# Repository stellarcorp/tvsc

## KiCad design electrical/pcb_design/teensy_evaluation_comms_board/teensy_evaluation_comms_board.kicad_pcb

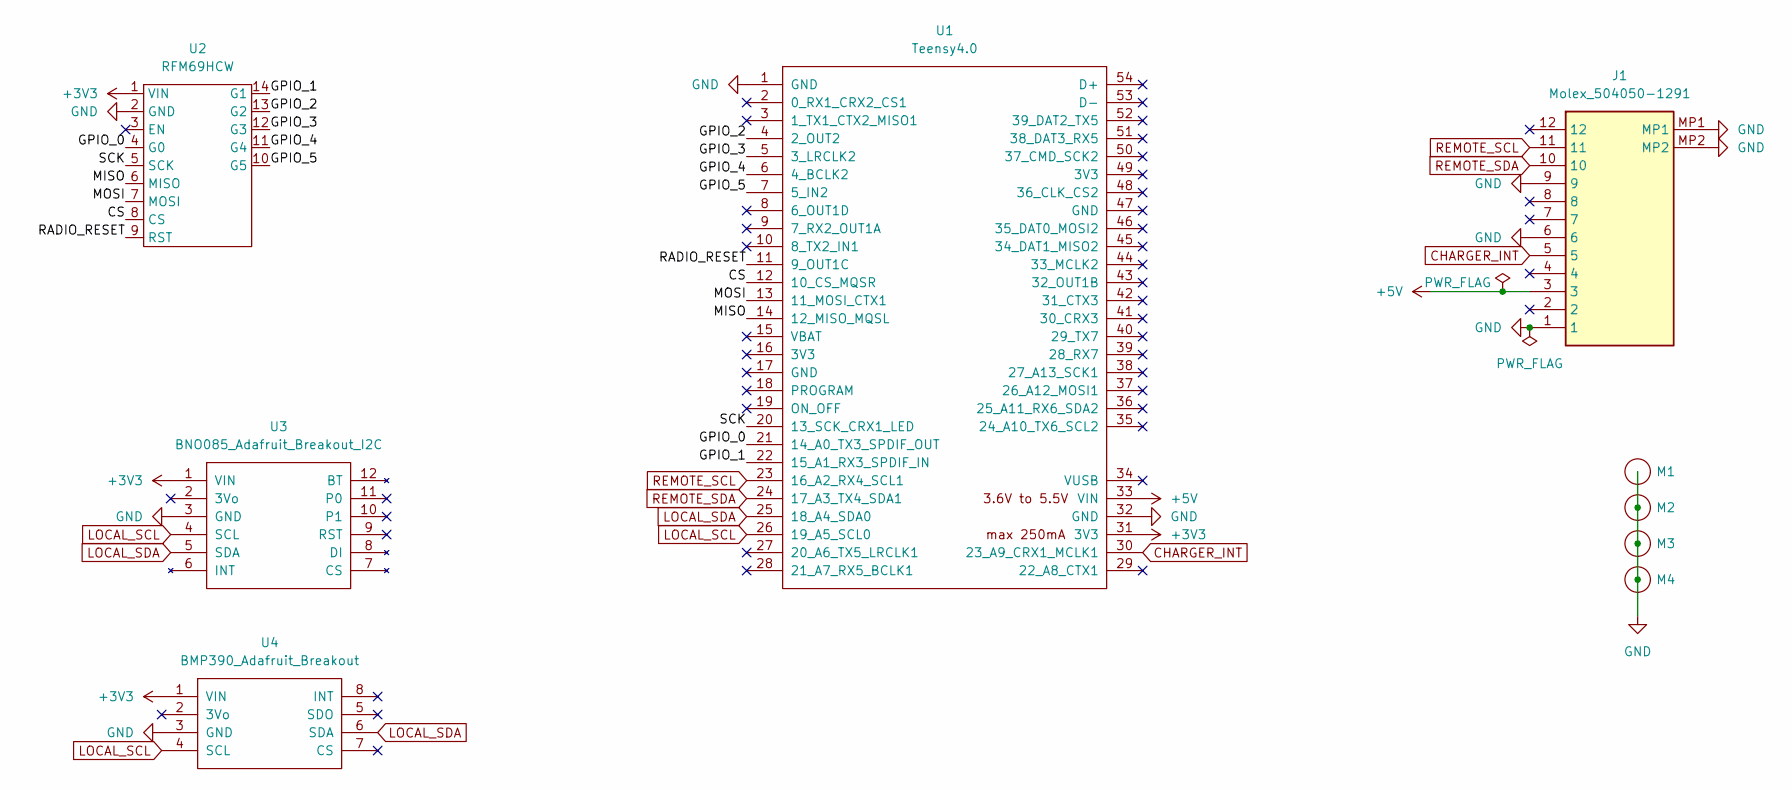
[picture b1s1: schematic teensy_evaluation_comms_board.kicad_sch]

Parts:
J1: Molex_504050-1291; 5040501291; Manufacturer_Part_Number 504050-1291; Mouser Part Number 538-504050-1291
M1, M2, M3, M4: MountingHole_3.2mm_M3_ISO7380_Pad_TopBottom
U1: Teensy4.0; Teensy40
U2: RFM69HCW; RFM69HCW_Adafruit_Breakout
U3: BNO085_Adafruit_Breakout_I2C; BNO085_Adafruit_Breakout
U4: BMP390_Adafruit_Breakout

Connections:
+3V3: U1.31 (3V3), U2.1 (VIN), U3.1 (VIN), U4.1 (VIN)
+5V: J1.3, U1.33 (VIN)
/CS: U1.12 (10_CS_MQSR), U2.8 (CS)
/GPIO_0: U1.21 (14_A0_TX3_SPDIF_OUT), U2.4 (G0)
/GPIO_1: U1.22 (15_A1_RX3_SPDIF_IN), U2.14 (G1)
/GPIO_2: U1.4 (2_OUT2), U2.13 (G2)
/GPIO_3: U1.5 (3_LRCLK2), U2.12 (G3)
/GPIO_4: U1.6 (4_BCLK2), U2.11 (G4)
/GPIO_5: U1.7 (5_IN2), U2.10 (G5)
/MISO: U1.14 (12_MISO_MQSL), U2.6 (MISO)
/MOSI: U1.13 (11_MOSI_CTX1), U2.7 (MOSI)
/RADIO_RESET: U1.11 (9_OUT1C), U2.9 (RST)
/SCK: U1.20 (13_SCK_CRX1_LED), U2.5 (SCK)
CHARGER_INT: J1.5, U1.30 (23_A9_CRX1_MCLK1)
GND: J1.1, J1.6, J1.9, J1.MP1, J1.MP2, M1.1 (Hole), M2.1 (Hole), M3.1 (Hole), M4.1 (Hole), U1.1 (GND), U1.32 (GND), U2.2 (GND), U3.3 (GND), U4.3 (GND)
LOCAL_SCL: U1.26 (19_A5_SCL0), U3.4 (SCL), U4.4 (SCL)
LOCAL_SDA: U1.25 (18_A4_SDA0), U3.5 (SDA), U4.6 (SDA)
REMOTE_SCL: J1.11, U1.23 (16_A2_RX4_SCL1)
REMOTE_SDA: J1.10, U1.24 (17_A3_TX4_SDA1)

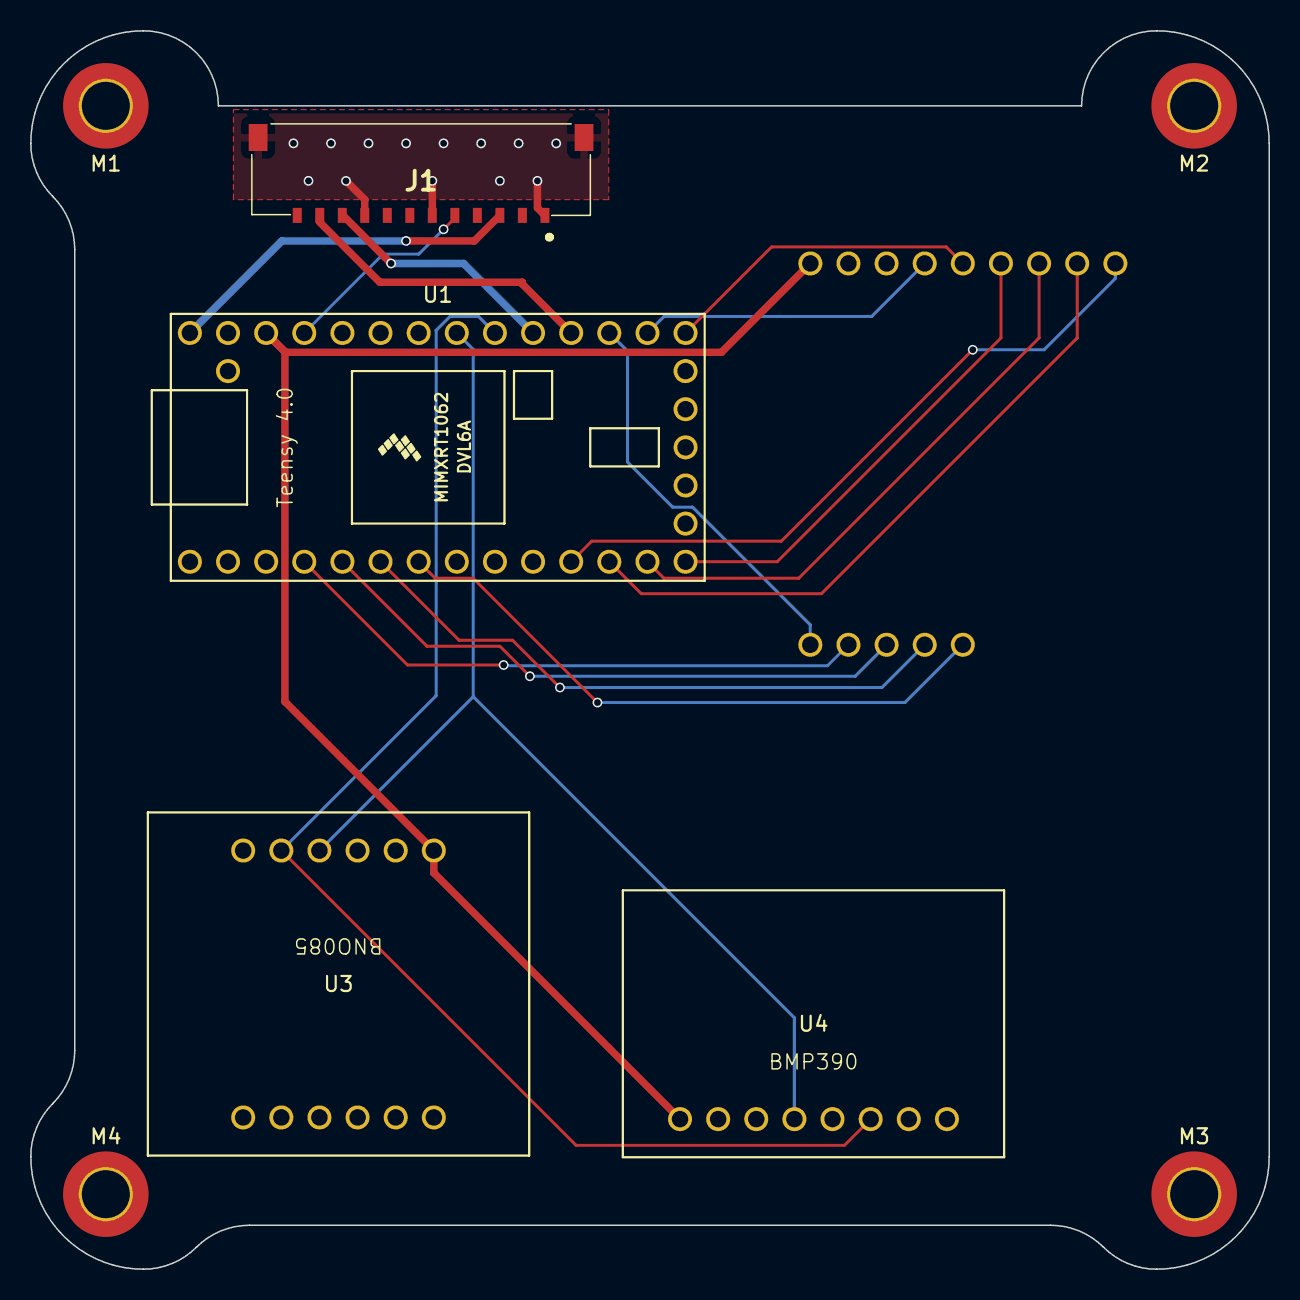
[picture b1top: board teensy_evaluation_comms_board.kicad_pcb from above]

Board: 2 copper layers, 82.5 x 82.5 mm, 9 parts (1 on the bottom side), 19 nets.

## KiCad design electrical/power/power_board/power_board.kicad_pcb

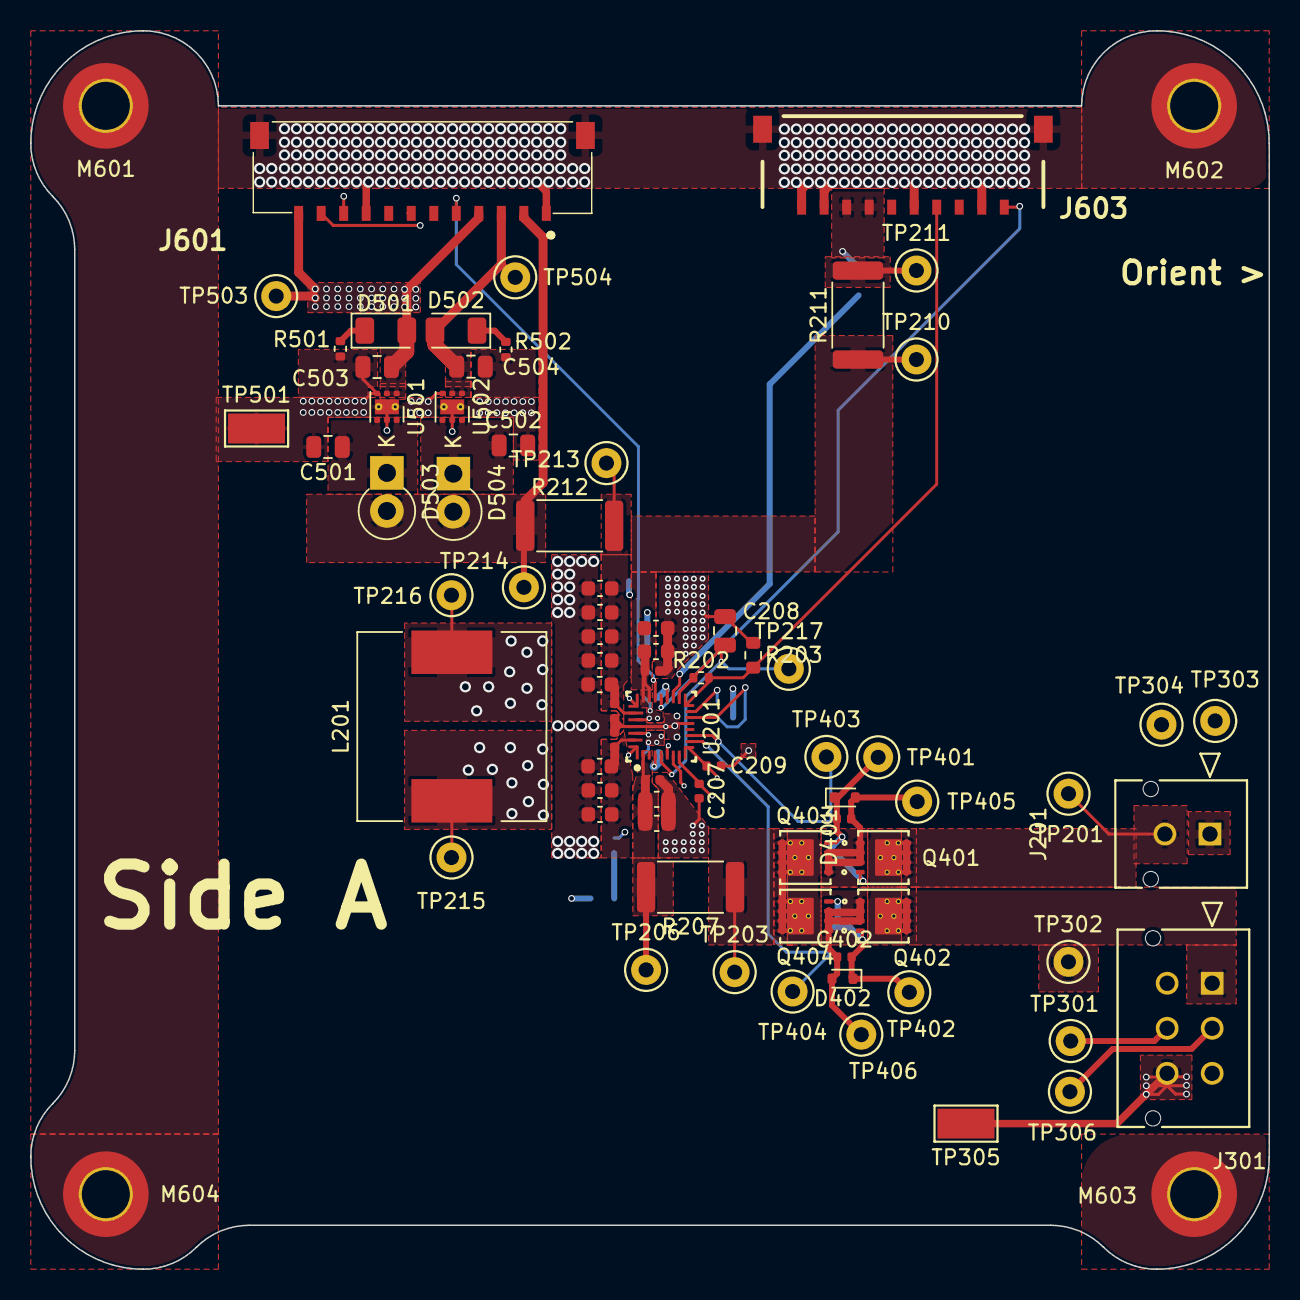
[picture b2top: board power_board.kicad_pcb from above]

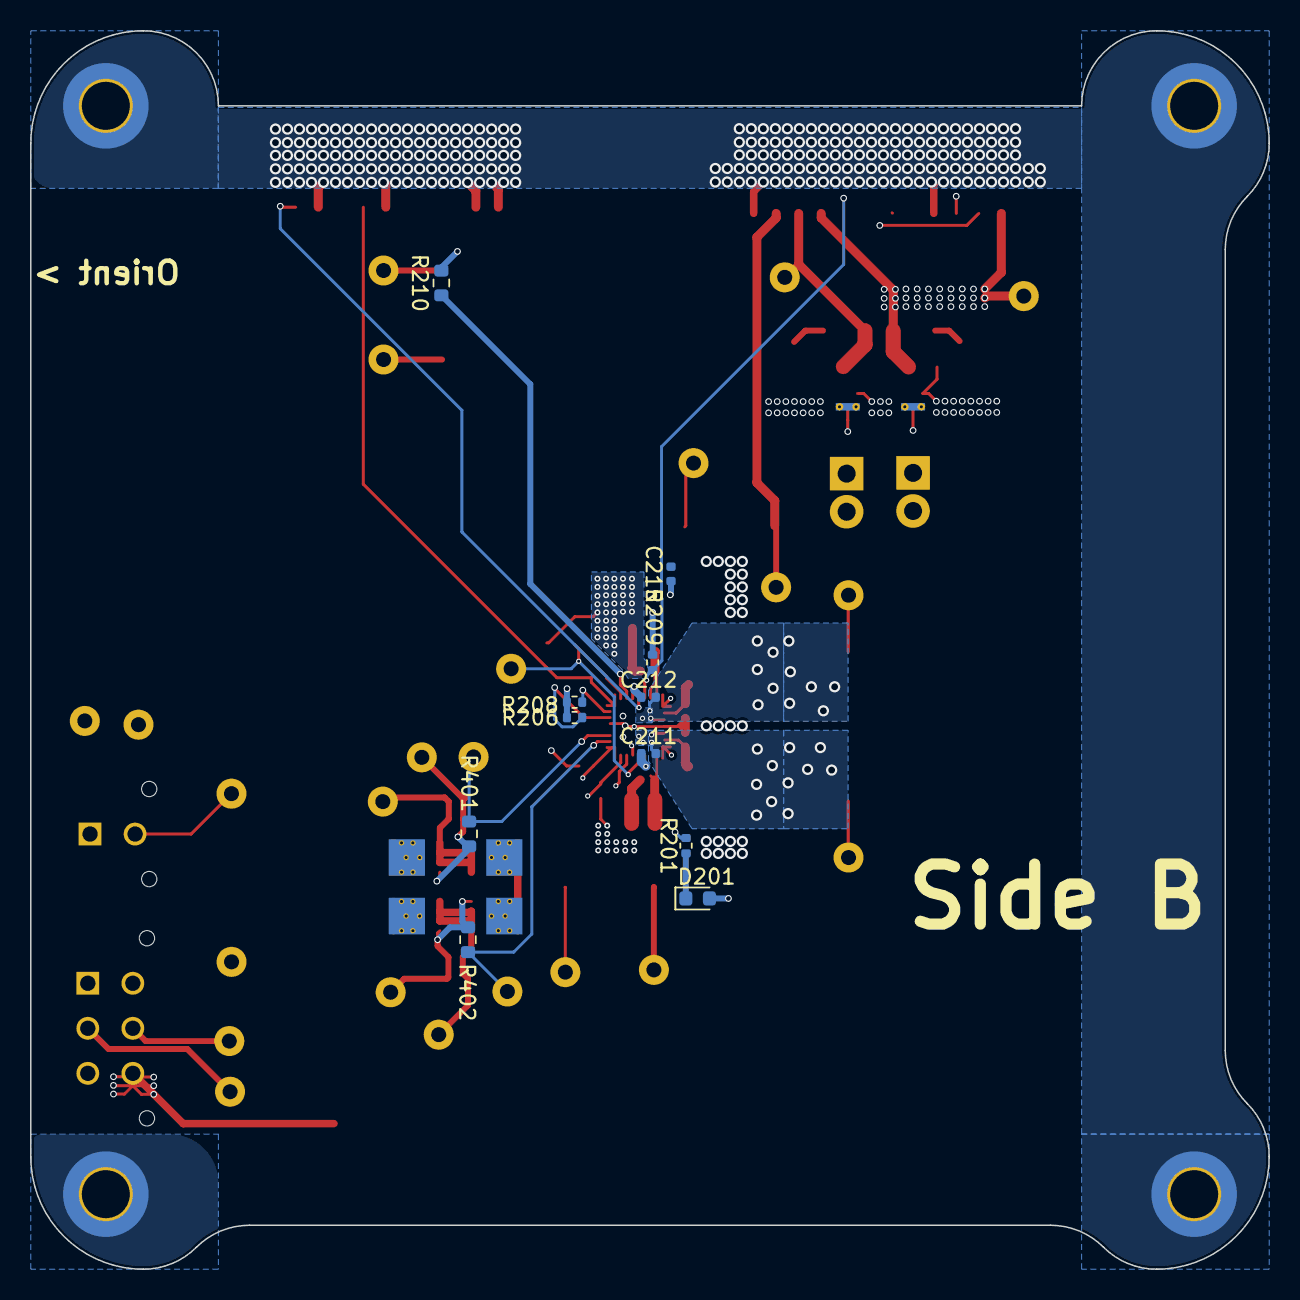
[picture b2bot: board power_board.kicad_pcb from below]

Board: 4 copper layers, 82.5 x 82.5 mm, 90 parts (11 on the bottom side), 40 nets.

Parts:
C201, C202, C203, C205, C206, C214, C216, C217, C218, C219, C220, C221: 10u; C_0603_1608Metric
C204, C207, C209, C210, C213, C222: 0.1u; C_0402_1005Metric
C208: 4.7u; C_0805_2012Metric
C211, C212: 0.047u; C_0402_1005Metric
C215, C401, C402: 1n; C_0402_1005Metric
C501, C502: 1u; C_0805_2012Metric
C503, C504: 2.2u; C_0805_2012Metric
D201: Green LED; LED_0603_1608Metric
D401, D402: 12V; D_SOD-523
D501, D502: White LED; LED_1206_3216Metric
D503, D504: 3A; D_DO-15_P2.54mm_Vertical_KathodeUp
J201: Molex_430450212
J301: Molex_430450612
J601: 504050-1291; 5040501291
J603: 504050-1091
L201: 1uH; L_12x12mm_H8mm
M601, M602, M603, M604: MountingHole_3.2mm_M3_ISO7380_Pad_TopBottom
Q401, Q402, Q403, Q404: CSD17581Q3A; Q3A_TEX
R201: 2.21k; R_0402_1005Metric
R202: 5.24k; R_0402_1005Metric
R203: 30.31k; R_0603_1608Metric
R206, R208, R209: 10k; R_0402_1005Metric
R207, R211, R212: 0.01; R_2512_6332Metric
R210: 100; R_0603_1608Metric
R401, R402: 294; R_0603_1608Metric
R501: 68; R_0402_1005Metric
R502: 150; R_0402_1005Metric
TP201, TP203, TP206, TP210, TP211, TP213, TP214, TP215, TP216, TP217, TP303, TP304, TP405, TP406: White; TestPoint_Keystone_5000-5004_Miniature
TP301, TP306, TP403, TP404: Black; TestPoint_Keystone_5000-5004_Miniature
TP302, TP401, TP402, TP503, TP504: Red; TestPoint_Keystone_5000-5004_Miniature
TP305, TP501: Ring; TestPoint_Keystone_5019_Minature
U201: BQ25798RQMR; RQM0029A-MFG
U501: TLV76733DRVx; WSON-6-1EP_2x2mm_P0.65mm_EP1x1.6mm_ThermalVias
U502: TLV76750DRVx; WSON-6-1EP_2x2mm_P0.65mm_EP1x1.6mm_ThermalVias

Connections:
+3.3V: C503.1, D201.2 (A), D501.2 (A), J601.4, J601.12, R206.1, R208.1, R209.1, TP503.1, U501.1 (OUT), U501.2 (SNS)
+5V: C504.1, D502.2 (A), J601.3, TP504.1, U502.1 (OUT), U502.2 (SNS)
/Charger/BAT: C216.1, C218.1, C222.1, R211.1, TP210.1, U201.22 (BAT), U201.23 (BAT)
/Charger/BATP: R210.1, U201.18 (BATP)
/Charger/BTST1: C211.1, U201.4 (BTST1)
/Charger/BTST2: C212.1, U201.19 (BTST2)
/Charger/PMID: C201.1, C202.1, C203.1, C204.1, U201.29 (PMID)
/Charger/REGN: C208.1, R202.1, TP217.1, U201.5 (REGN), U201.17 (ILIM_HIZ)
/Charger/STAT: R201.2, U201.1 (STAT)
/Charger/SW1: C211.2, L201.1, TP215.1, U201.28 (SW1)
/Charger/SW2: C212.2, L201.2, TP216.1, U201.26 (SW2)
/Charger/SYS: C213.1, C214.1, C217.1, C219.1, C220.1, C221.1, R212.1, TP213.1, U201.25 (SYS)
/Charger/VBUS_PIN: C205.1, C206.1, C210.1, R207.2, TP206.1, U201.2 (VBUS), U201.3 (VBUS)
/Input Selection/ACDRV1_SOURCE: C401.1, D401.2 (A), Q401.1 (S), Q403.1 (S), TP405.1
/Input Selection/ACDRV2_SOURCE: C402.1, D402.2 (A), Q402.1 (S), Q404.1 (S), TP406.1
/Input Selection/SOLAR_VBUS_GATE: C401.2, D401.1 (K), Q401.4 (G), Q403.4 (G), R401.1, TP401.1
/Input Selection/USB_VBUS_GATE: C402.2, D402.1 (K), Q402.4 (G), Q404.4 (G), R402.1, TP402.1
/USB/USB_CC1: J301.2, TP306.1
/USB/USB_CC2: J301.5, TP301.1
ACDRV1: R401.2, TP403.1, U201.11 (ACDRV1)
ACDRV2: R402.2, TP404.1, U201.10 (ACDRV2)
BATTERY_+: J603.3, J603.4, R210.2, R211.2, TP211.1
BATTERY_ID: J603.10, U201.20 (PROG)
CHARGER_INT: J601.5, R209.2, U201.21 (INT_N)
GND: C201.2, C202.2, C203.2, C204.2, C205.2, C206.2, C207.2, C208.2, C209.2, C210.2, C213.2, C214.2, C215.2, C216.2, C217.2, C218.2, C219.2, C220.2, C221.2, C222.2, C501.2, C502.2, C503.2, C504.2, J201.1, J301.6, J601.1, J601.6, J601.9, J601.MP1, J601.MP2, J603.1, J603.2, J603.6, J603.9, J603.11 (MP1), J603.12 (MP2), M601.1 (Hole), M602.1 (Hole), M603.1 (Hole), M604.1 (Hole), R203.2, R501.2, R502.2, TP305.1, TP501.1, U201.13 (CE_N), U201.27 (GND), U501.3 (GND), U501.5 (GND), U501.7 (PAD), U502.3 (GND), U502.5 (GND), U502.7 (PAD)
unnamed: D201.1 (K), R201.1
unnamed: D501.1 (K), R501.1
unnamed: D502.1 (K), R502.1
unnamed: C501.1, D503.1 (K), U501.4 (EN), U501.6 (IN)
unnamed: C502.1, D504.1 (K), U502.4 (EN), U502.6 (IN)
unnamed: C215.1, U201.24 (SDRV)
POWER_SCL: J601.11, R206.2, U201.14 (SCL)
POWER_SDA: J601.10, R208.2, U201.15 (SDA)
SOLAR_VBUS: C209.1, J201.2, Q401.5 (D), TP201.1, U201.9 (VAC1)
THERMISTOR: J603.7, R202.2, R203.1, U201.16 (TS)
USB_D+: J301.3, TP303.1, U201.6 (D+)
USB_D-: J301.4, TP304.1, U201.7 (D-)
USB_VBUS: C207.1, J301.1, Q402.5 (D), TP302.1, U201.8 (VAC2)
VBUS: Q403.5 (D), Q404.5 (D), R207.1, TP203.1
VCC: D503.2 (A), D504.2 (A), J601.2, R212.2, TP214.1

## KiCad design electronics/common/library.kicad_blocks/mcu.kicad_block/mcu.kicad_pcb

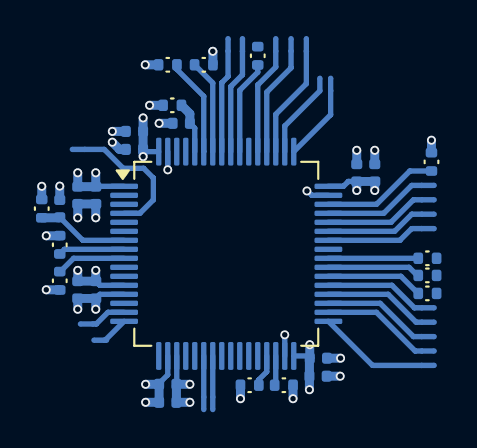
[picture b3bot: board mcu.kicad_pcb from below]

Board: 4 copper layers, 49 parts (49 on the bottom side), 36 nets.

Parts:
C101, C102, C105, C106, C108, C109, C111, C112: 100n; Nondescript_C_0402_1005Metric
C103, C104, C107, C110, C113, C114: 1u; Nondescript_C_0402_1005Metric
NT101, NT102, NT103, NT104, NT105, NT106, NT107, NT108, NT109, NT110, NT111, NT112, NT113, NT114, NT115, NT116, NT117, NT118, NT119, NT120, NT121: NetTie_2; NetTie-2_SMD_Pad0.3mm
R101, R105, R106, R107, R108, R109, R110, R111, R112: 9k31; Nondescript_R_0402_1005Metric
R102, R103, R104, R113: 33; Nondescript_R_0402_1005Metric
U101: STM32L452RCTx; LQFP-64_10x10mm_P0.5mm

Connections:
/mcu/3V3: C103.1, C104.1, C105.1, C106.1, C107.1, C108.1, C109.1, C110.1, C111.1, C112.1, C113.1, C114.1, R101.1, R105.1, R107.1, R108.1, R109.1, R110.1, R111.1, R112.1, U101.1 (VBAT), U101.13 (VDDA), U101.19 (VDD), U101.32 (VDD), U101.48 (VDDUSB), U101.64 (VDD)
/mcu/BOARD_ID_PWR_INTERNAL: NT111.1, U101.22 (PA6)
/mcu/BOARD_ID_SENS_INTERNAL: NT112.1, U101.23 (PA7)
/mcu/BOARD_ID_VERSION_INTERNAL: NT110.1, U101.16 (PA2)
/mcu/BOOT0: C101.1, R106.1, U101.60 (PH3)
/mcu/CAN1_RX_INTERNAL: NT108.1, U101.44 (PA11)
/mcu/CAN1_SHUTDOWN_INTERNAL: NT106.1, U101.42 (PA9)
/mcu/CAN1_SILENT_INTERNAL: NT107.1, U101.43 (PA10)
/mcu/CAN1_TX_INTERNAL: NT109.1, U101.45 (PA12)
/mcu/DEBUG_LED_INTERNAL: NT105.2, U101.4 (PC15)
/mcu/I2C1_SCL: R108.2, U101.58 (PB6)
/mcu/I2C1_SDA: R111.2, U101.59 (PB7)
/mcu/I2C2_SCL: R109.2, U101.29 (PB10)
/mcu/I2C2_SDA: R112.2, U101.30 (PB11)
/mcu/I2C3_SCL: R101.2, U101.8 (PC0)
/mcu/I2C3_SDA: R107.2, U101.9 (PC1)
/mcu/NRST: C102.1, R105.2, U101.7 (NRST)
/mcu/NRST_CTRL_INTERNAL: R102.1, U101.38 (PC7)
/mcu/SPI1_MISO_INTERNAL: NT116.1, U101.56 (PB4)
/mcu/SPI1_MOSI_INTERNAL: NT117.1, U101.57 (PB5)
/mcu/SPI1_SCK_INTERNAL: NT114.1, U101.15 (PA1)
/mcu/SPI1_SPI3_CS_INTERNAL: NT115.1, U101.50 (PA15)
/mcu/SPI2_CS_INTERNAL: NT118.1, U101.33 (PB12)
/mcu/SPI2_MISO_INTERNAL: NT120.1, U101.35 (PB14)
/mcu/SPI2_MOSI_INTERNAL: NT121.1, U101.36 (PB15)
/mcu/SPI2_SCK_INTERNAL: NT119.1, U101.34 (PB13)
/mcu/SPI3_MISO_INTERNAL: NT103.2, U101.52 (PC11)
/mcu/SPI3_MOSI_INTERNAL: NT104.2, U101.53 (PC12)
/mcu/SPI3_SCK_INTERNAL: NT102.2, U101.51 (PC10)
/mcu/SWCLK_CTRL_INTERNAL: R104.1, U101.40 (PC9)
/mcu/SWCLK_INTERNAL: NT113.1, U101.49 (PA14)
/mcu/SWDIO: R110.2, U101.46 (PA13)
/mcu/SWDIO_CTRL_INTERNAL: R103.1, U101.39 (PC8)
/mcu/SWO_CTRL_INTERNAL: NT101.2, U101.37 (PC6)
GND: C101.2, C102.2, C103.2, C104.2, C105.2, C106.2, C107.2, C108.2, C109.2, C110.2, C111.2, C112.2, C113.2, C114.2, R106.2, U101.12 (VSSA), U101.18 (VSS), U101.31 (VSS), U101.47 (VSS), U101.63 (VSS)
unnamed: R113.1, U101.55 (PB3)

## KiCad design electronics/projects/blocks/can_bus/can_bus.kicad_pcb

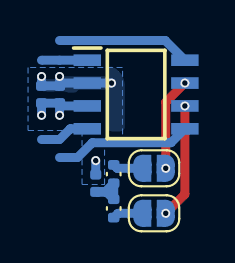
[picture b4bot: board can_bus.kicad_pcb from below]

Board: 4 copper layers, 12 parts (12 on the bottom side), 11 nets.

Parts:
C101: 1u; Nondescript_C_0402_1005Metric
C102, C103: 100n; Nondescript_C_0402_1005Metric
JP101, JP102: SolderJumper_2_Open; SolderJumper-2_P1.3mm_Open_RoundedPad1.0x1.5mm
NT701, NT702, NT703, NT704: NetTie_2; NetTie-2_SMD_Pad0.5mm
R101, R102: 60; Nondescript_R_0402_1005Metric
U101: TCAN330DR; SOIC127P600X175-8N

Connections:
/can_bus/3V3: C101.1, C102.1, U101.3 (VCC)
/can_bus/CANH: JP101.1 (A), U101.7 (CANH)
/can_bus/CANH_TERMINATION: JP101.2 (B), R101.1
/can_bus/CANL: JP102.2 (B), U101.6 (CANL)
/can_bus/CANL_TERMINATION: JP102.1 (A), R102.2
GND: C101.2, C102.2, C103.1, U101.2 (GND)
unnamed: C103.2, R101.2, R102.1
unnamed: NT703.2, U101.4 (RXD)
unnamed: NT701.2, U101.8 (S)
unnamed: NT704.2, U101.5 (SHDN)
unnamed: NT702.2, U101.1 (TXD)

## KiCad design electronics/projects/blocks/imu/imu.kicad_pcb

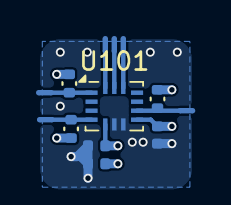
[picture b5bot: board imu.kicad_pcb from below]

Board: 4 copper layers, 13 parts (13 on the bottom side), 8 nets.

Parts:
C101: 1u; Nondescript_C_0402_1005Metric
C102, C103: 100n; Nondescript_C_0402_1005Metric
NT101, NT102, NT103, NT104, NT105, NT106: NetTie_2; NetTie-2_SMD_Pad0.3mm
R101, R106, R107: 9k31; Nondescript_R_0402_1005Metric
U101: BMI323; Bosch_LGA-14_3x2.5mm_P0.5mm

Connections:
/imu/3V3: C101.1, C102.1, C103.1, R101.1, R106.1, R107.1, U101.5 (VDDIO), U101.8 (VDD)
GND: C101.2, C102.2, C103.2, U101.6 (GNDIO), U101.7 (GND)
unnamed: NT101.2, U101.12 (CSB)
unnamed: NT105.1, R107.2, U101.4 (INT1)
unnamed: NT106.1, R106.2, U101.9 (INT2)
unnamed: NT102.2, U101.13 (SCx)
unnamed: NT104.2, R101.2, U101.1 (SDO)
unnamed: NT103.2, U101.14 (SDx)

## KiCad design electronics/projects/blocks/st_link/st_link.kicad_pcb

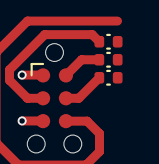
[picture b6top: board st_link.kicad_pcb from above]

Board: 4 copper layers, 4 parts (0 on the bottom side), 3 nets.

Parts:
J601: STLINK; Tag-Connect_TC2030-IDC-NL_2x03_P1.27mm_Vertical
R601, R602, R603: 33; Nondescript_R_0402_1005Metric

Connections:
unnamed: J601.3 (T_NRST), R602.2
unnamed: J601.4 (T_SWCLK), R603.2
unnamed: J601.2 (T_SWDIO), R601.2

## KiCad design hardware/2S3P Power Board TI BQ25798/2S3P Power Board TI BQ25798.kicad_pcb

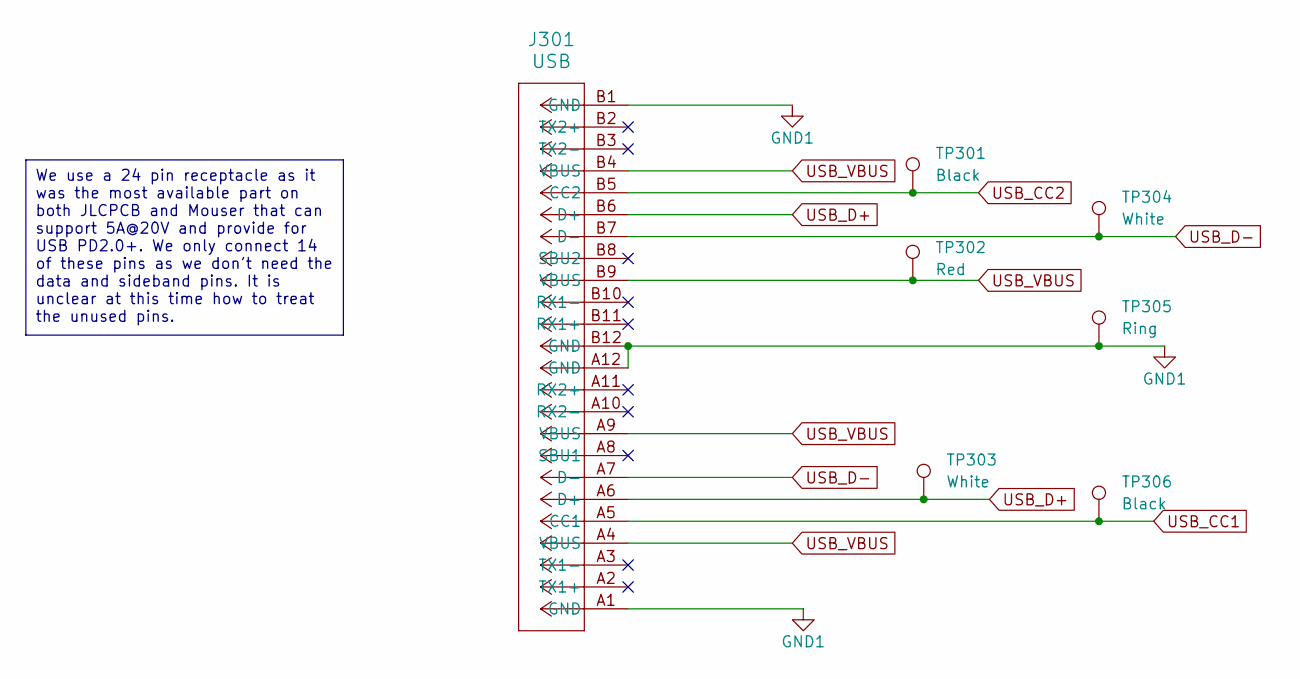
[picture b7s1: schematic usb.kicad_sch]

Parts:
J301: USB; CONN_124018612112A_AMP; MPN C464605
TP301, TP306: Black; TestPoint_Keystone_5000-5004_Miniature; MPN C238122
TP302: Red; TestPoint_Keystone_5000-5004_Miniature; MPN C5199900
TP303, TP304: White; TestPoint_Keystone_5000-5004_Miniature; MPN C238123
TP305: Ring; TestPoint_Keystone_5019_Minature; MPN C238131

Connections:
GND1: J301.A1 (GND), J301.A12 (GND), J301.B1 (GND), J301.B12 (GND), TP305.1; also elsewhere on the board
USB_CC1: J301.A5 (CC1), TP306.1
USB_CC2: J301.B5 (CC2), TP301.1
USB_D+: J301.A6 (D+), J301.B6 (D+), TP303.1; also elsewhere on the board
USB_D-: J301.A7 (D-), J301.B7 (D-), TP304.1; also elsewhere on the board
USB_VBUS: J301.A4 (VBUS), J301.A9 (VBUS), J301.B4 (VBUS), J301.B9 (VBUS), TP302.1; also elsewhere on the board

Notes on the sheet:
We use a 24 pin receptacle as it was the most available part on both JLCPCB and Mouser that can support 5A@20V and provide for USB PD2.0+. We only connect 14 of these pins as we don't need the data and sideband pins. It is unclear at this time how to treat the unused pins.

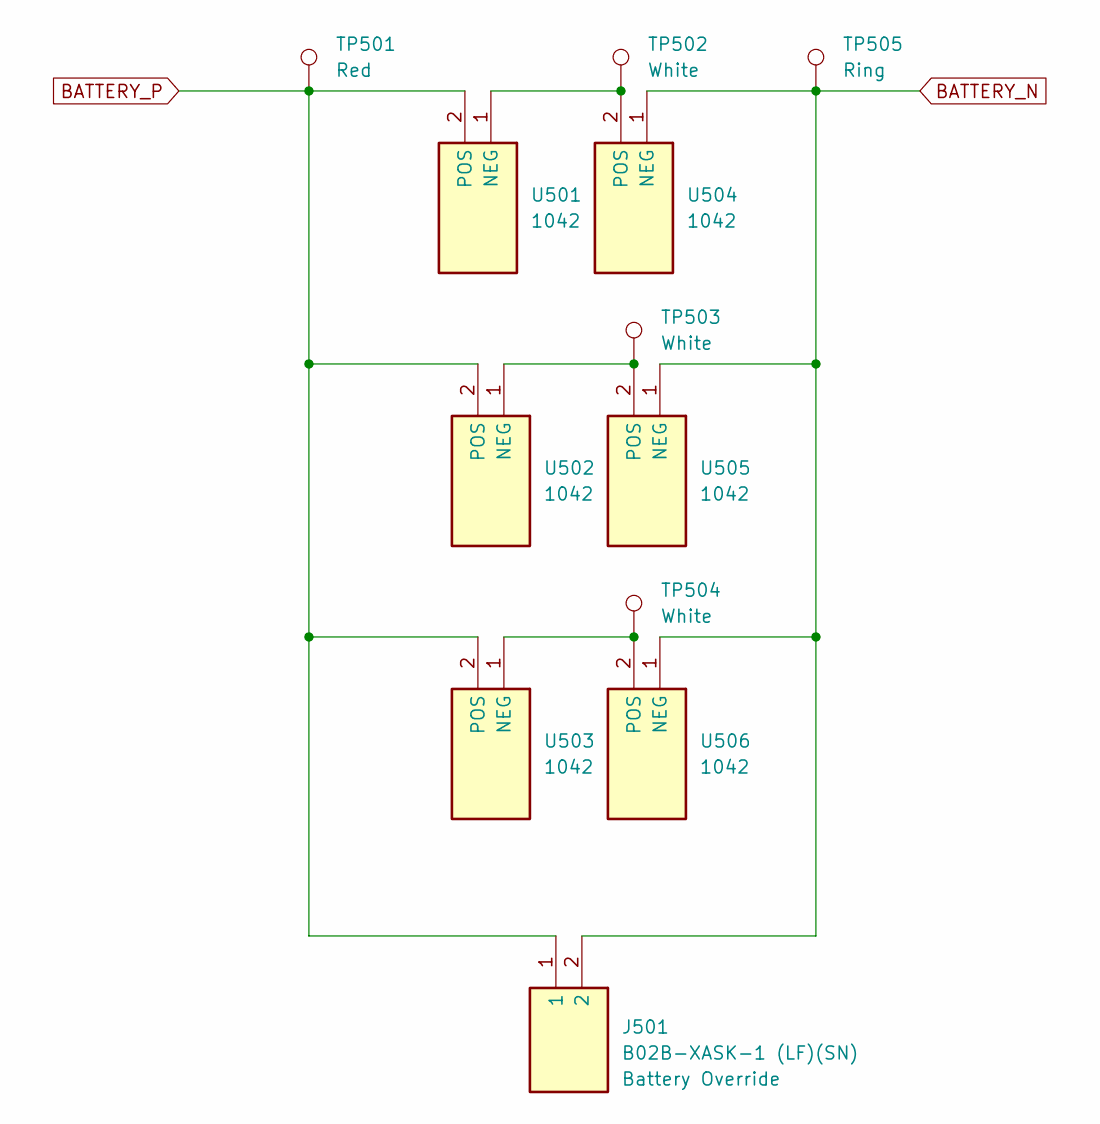
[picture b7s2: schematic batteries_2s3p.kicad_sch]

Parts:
J501: B02B-XASK-1 (LF)(SN); B02BXASK1LFSN; Manufacturer_Part_Number B02B-XASK-1 (LF)(SN)
TP501: Red; TestPoint_Keystone_5000-5004_Miniature; MPN C5199900
TP502, TP503, TP504: White; TestPoint_Keystone_5000-5004_Miniature; MPN C238123
TP505: Ring; TestPoint_Keystone_5019_Minature; MPN C238131
U501, U502, U503, U504, U505, U506: 1042; KEYSTONE-1042; Manufacturer_Part_Number 1042; Mouser Part Number 534-1042

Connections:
BATTERY_N: J501.2, TP505.1, U504.1 (NEG), U505.1 (NEG), U506.1 (NEG); also elsewhere on the board
BATTERY_P: J501.1, TP501.1, U501.2 (POS), U502.2 (POS), U503.2 (POS); also elsewhere on the board
unnamed: TP502.1, U501.1 (NEG), U504.2 (POS)
unnamed: TP503.1, U502.1 (NEG), U505.2 (POS)
unnamed: TP504.1, U503.1 (NEG), U506.2 (POS)

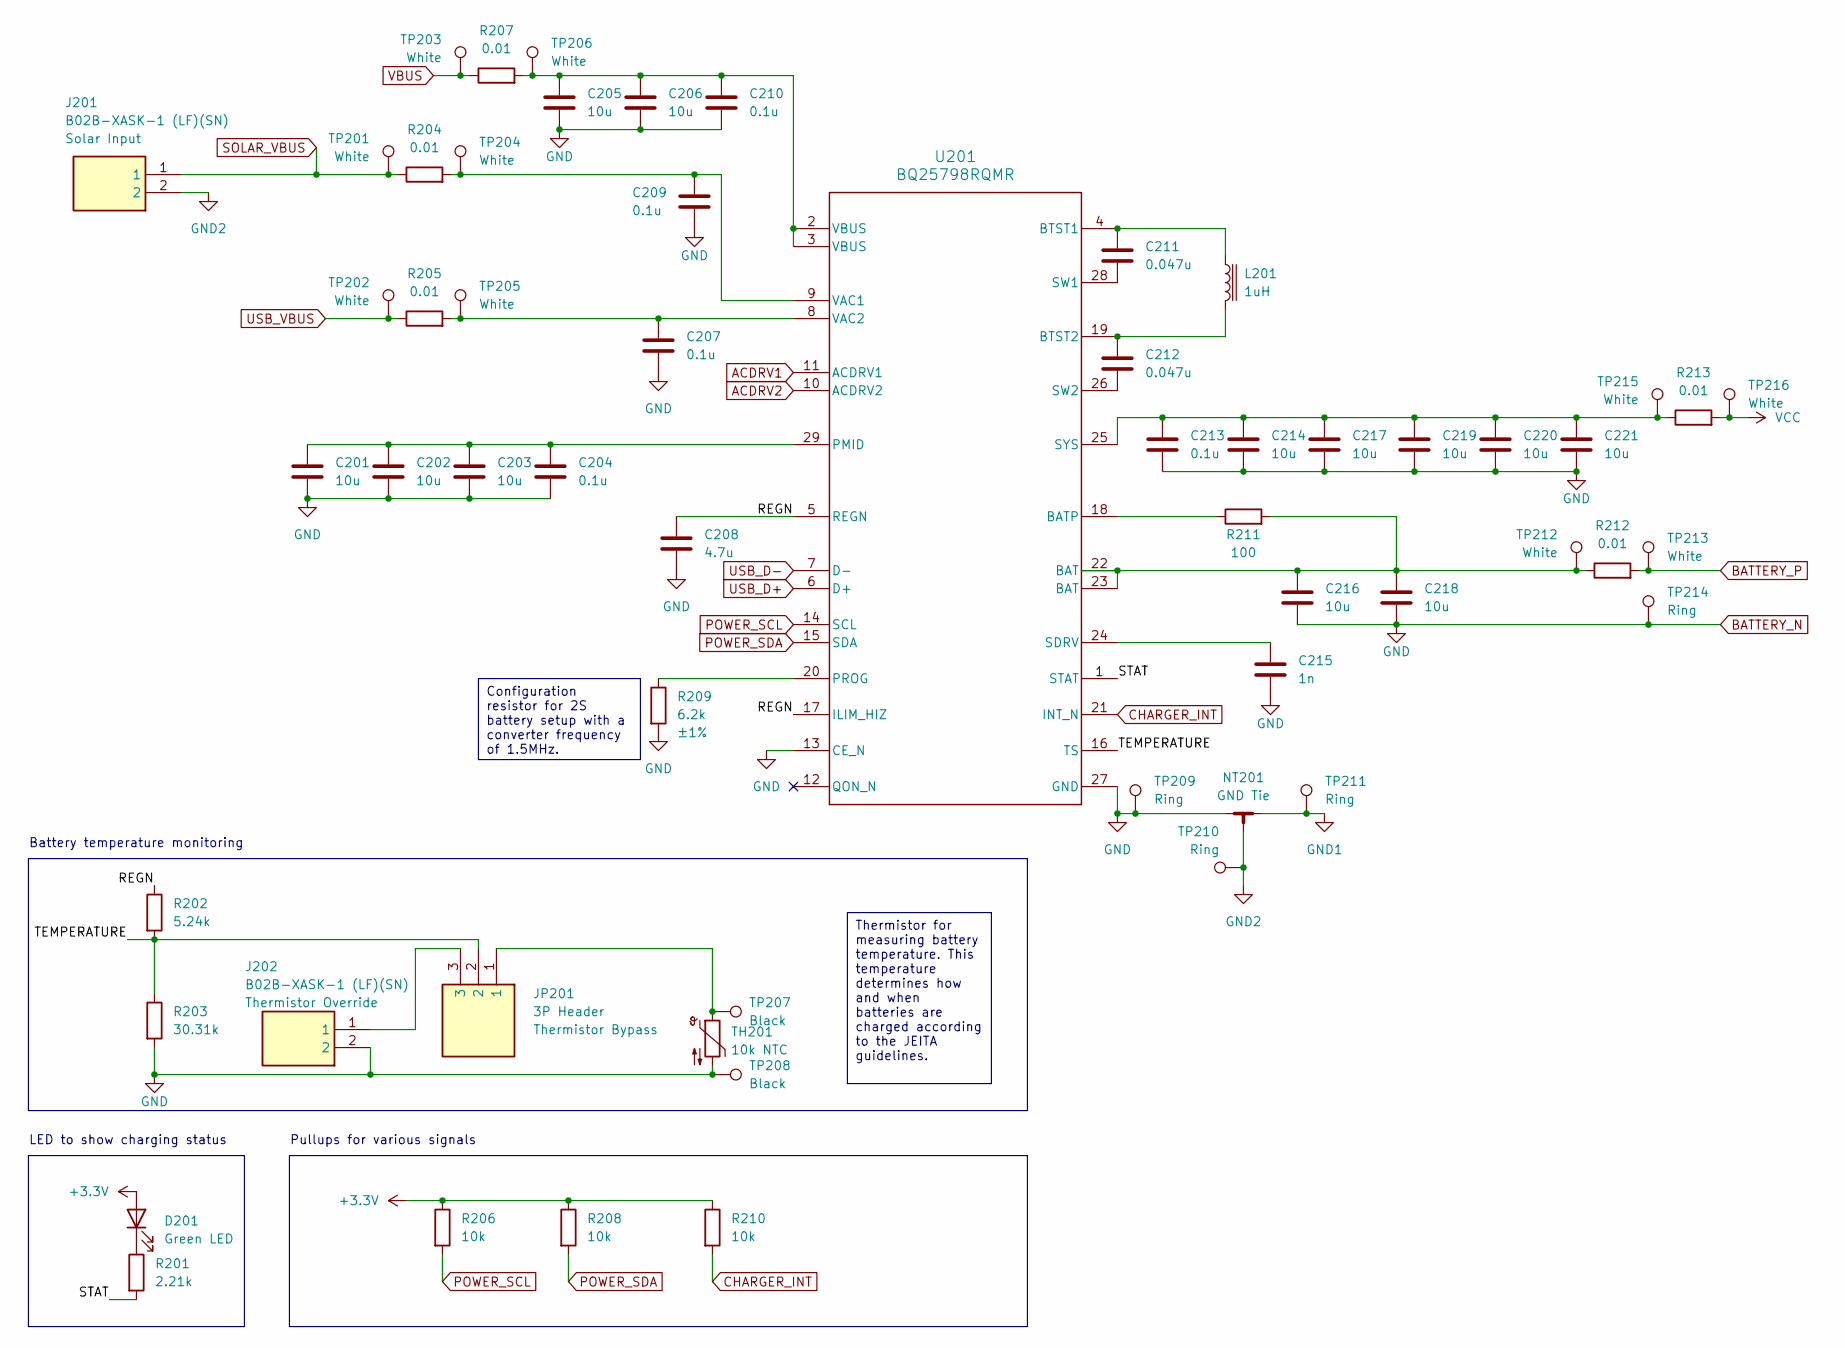
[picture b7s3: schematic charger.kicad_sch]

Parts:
C201, C202, C203, C205, C206, C214, C217, C219, C220, C221: 10u; C_0603_1608Metric; Manufacturer Part Number GRT188R61E106ME13D
C204, C207, C209, C210, C213: 0.1u; C_0402_1005Metric; Manufacturer Part Number GCJ188R71H104KA12D
C208: 4.7u; C_0805_2012Metric; MPN C338100
C211, C212: 0.047u; C_0402_1005Metric; Manufacturer Part Number CL05B473KA5NNNC
C215: 1n; C_0402_1005Metric; MPN C76947
C216, C218: 10u; C_0603_1608Metric; MPN C697423
D201: Green LED; LED_0603_1608Metric; MPN C125093
J201, J202: B02B-XASK-1 (LF)(SN); B02BXASK1LFSN; Manufacturer_Part_Number B02B-XASK-1 (LF)(SN)
JP201: 3P Header; HDRV3W64P0X254_1X3_762X254X869P; Manufacturer_Part_Number 61300311121; Mouser Part Number 710-61300311121
L201: 1uH; L_12x12mm_H8mm; MPN C2998763
NT201: GND Tie
R201: 2.21k; R_0402_1005Metric; MPN C305298
R202: 5.24k; R_0402_1005Metric; MPN C170332
R203: 30.31k; R_0603_1608Metric; MPN C423049
R204, R205, R207, R212, R213: 0.01; R_2512_6332Metric; MPN C844296
R206, R208, R210: 10k; R_0402_1005Metric; MPN C71617
R209: 6.2k; R_0603_1608Metric; Tolerance ±1%; MPN C114631
R211: 100; R_0603_1608Metric; MPN C105588
TH201: 10k NTC; R_0402_1005Metric; MPN C336815
TP201, TP202, TP203, TP204, TP205, TP206, TP212, TP213, TP215, TP216: White; TestPoint_Keystone_5000-5004_Miniature; MPN C238123
TP207, TP208: Black; TestPoint_Keystone_5000-5004_Miniature; MPN C238122
TP209, TP210, TP211, TP214: Ring; TestPoint_Keystone_5019_Minature; MPN C238131
U201: BQ25798RQMR; RQM0029A-MFG; MPN C2876593

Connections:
+3.3V: D201.2 (A), R206.1, R208.1, R210.1; also elsewhere on the board
/Charger/REGN: C208.1, R202.1, U201.5 (REGN), U201.17 (ILIM_HIZ)
/Charger/STAT: R201.2, U201.1 (STAT)
/Charger/TEMPERATURE: JP201.2, R202.2, R203.1, U201.16 (TS)
ACDRV1: U201.11 (ACDRV1); also elsewhere on the board
ACDRV2: U201.10 (ACDRV2); also elsewhere on the board
BATTERY_N: C201.2, C202.2, C203.2, C204.2, C205.2, C206.2, C207.2, C208.2, C209.2, C210.2, C213.2, C214.2, C215.2, C216.2, C217.2, C218.2, C219.2, C220.2, C221.2, J202.2, NT201.1, R203.2, R209.2, TH201.2, TP208.1, TP209.1, TP214.1, U201.13 (CE_N), U201.27 (GND); also elsewhere on the board
BATTERY_P: R212.2, TP213.1; also elsewhere on the board
CHARGER_INT: R210.2, U201.21 (INT_N); also elsewhere on the board
GND1: NT201.2, TP211.1; also elsewhere on the board
GND2: J201.2, NT201.3, TP210.1
unnamed: C205.1, C206.1, C210.1, R207.2, TP206.1, U201.2 (VBUS), U201.3 (VBUS)
unnamed: C216.1, C218.1, R211.2, R212.1, TP212.1, U201.22 (BAT), U201.23 (BAT)
unnamed: D201.1 (K), R201.1
unnamed: J202.1, JP201.3
unnamed: JP201.1, TH201.1, TP207.1
unnamed: R211.1, U201.18 (BATP)
unnamed: C211.1, L201.1, U201.4 (BTST1)
unnamed: C212.1, L201.2, U201.19 (BTST2)
unnamed: C201.1, C202.1, C203.1, C204.1, U201.29 (PMID)
unnamed: R209.1, U201.20 (PROG)
unnamed: C215.1, U201.24 (SDRV)
unnamed: C211.2, U201.28 (SW1)
unnamed: C212.2, U201.26 (SW2)
unnamed: C213.1, C214.1, C217.1, C219.1, C220.1, C221.1, R213.1, TP215.1, U201.25 (SYS)
unnamed: C209.1, R204.2, TP204.1, U201.9 (VAC1)
unnamed: C207.1, R205.2, TP205.1, U201.8 (VAC2)
POWER_SCL: R206.2, U201.14 (SCL); also elsewhere on the board
POWER_SDA: R208.2, U201.15 (SDA); also elsewhere on the board
SOLAR_VBUS: J201.1, R204.1, TP201.1; also elsewhere on the board
USB_D+: U201.6 (D+); also elsewhere on the board
USB_D-: U201.7 (D-); also elsewhere on the board
USB_VBUS: R205.1, TP202.1; also elsewhere on the board
VBUS: R207.1, TP203.1; also elsewhere on the board
VCC: R213.2, TP216.1; also elsewhere on the board

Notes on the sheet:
Configuration resistor for 2S battery setup with a converter frequency of 1.5MHz.
Thermistor for measuring battery temperature. This temperature determines how and when batteries are charged according to the JEITA guidelines.
Pullups for various signals
Battery temperature monitoring
LED to show charging status

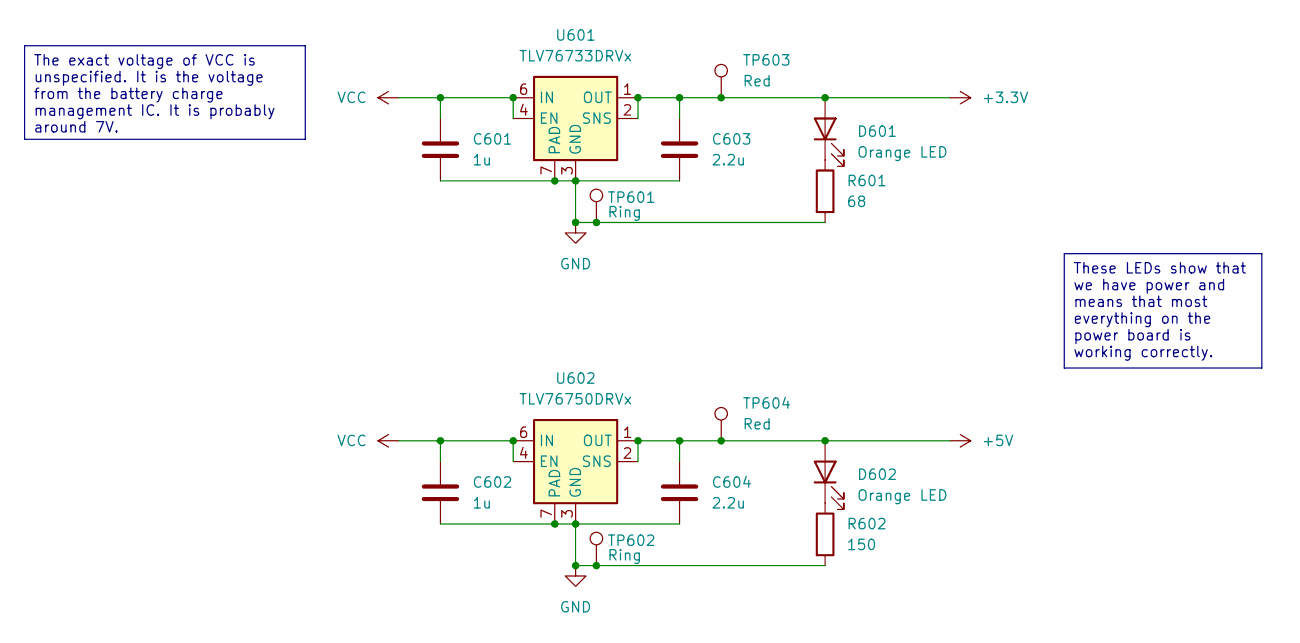
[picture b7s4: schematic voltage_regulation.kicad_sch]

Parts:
C601, C602: 1u; C_0805_2012Metric; MPN C726584
C603, C604: 2.2u; C_0805_2012Metric; MPN C577425
D601, D602: Orange LED; LED_1210_3225Metric; MPN C284943
R601: 68; R_0402_1005Metric; MPN C163455
R602: 150; R_0402_1005Metric; MPN C138054
TP601, TP602: Ring; TestPoint_Keystone_5019_Minature; MPN C238131
TP603, TP604: Red; TestPoint_Keystone_5000-5004_Miniature; MPN C5199900
U601: TLV76733DRVx; WSON-6-1EP_2x2mm_P0.65mm_EP1x1.6mm_ThermalVias; MPN C2848334
U602: TLV76750DRVx; WSON-6-1EP_2x2mm_P0.65mm_EP1x1.6mm_ThermalVias; Manufacturer Part Number TLV76750DRVR

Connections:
+3.3V: C603.1, D601.2 (A), TP603.1, U601.1 (OUT), U601.2 (SNS); also elsewhere on the board
+5V: C604.1, D602.2 (A), TP604.1, U602.1 (OUT), U602.2 (SNS); also elsewhere on the board
BATTERY_N: C601.2, C602.2, C603.2, C604.2, R601.2, R602.2, TP601.1, TP602.1, U601.3 (GND), U601.5 (GND), U601.7 (PAD), U602.3 (GND), U602.5 (GND), U602.7 (PAD); also elsewhere on the board
unnamed: D601.1 (K), R601.1
unnamed: D602.1 (K), R602.1
VCC: C601.1, C602.1, U601.4 (EN), U601.6 (IN), U602.4 (EN), U602.6 (IN); also elsewhere on the board

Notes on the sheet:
These LEDs show that we have power and means that most everything on the power board is working correctly.
The exact voltage of VCC is unspecified. It is the voltage from the battery charge management IC. It is probably around 7V.
